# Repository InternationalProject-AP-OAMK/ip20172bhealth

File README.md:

# 2bhealth
International Project BEL / FIN to develop an e-Health prototype with application to read-out the users' heartrate

## Working Android Studio code:
https://github.com/InternationalProject-AP-OAMK/ip20172bhealth/tree/master/Android_Studio/_workingProject

## Hardware documentation:
https://github.com/InternationalProject-AP-OAMK/ip20172bhealth/tree/master/Hardware/

## Fitrax (Solo) downloadable in the Play Store:
https://play.google.com/store/apps/details?id=com.nickenkoen.fitraxfinaldemo
- tested with Xiaomi Mi5S, 5.15inch, 1920x1080p, Android 7.1.1
- tested with Samsung Galaxy S4 mini, 4.3inch, 960x540p, Android 4.4.4
- tested with Motorola Moto X, 4.7inch, 1280x720p, Android 6.0

## Fitrax (Team) downloadable in the Play Store:
https://play.google.com/store/apps/details?id=com.nickenkoen.fitraxfinalcoachdemo
- tested with Samsung Galaxy Note 10.1, 10.1 inch, 1280x800p, Android 5.0 

!! Layout can differ between devices !!

## How to install/use:
1. Download Fitrax Solo on smartphone
2. Open and login with a new teamname and username
3. Tap the BlueTooth logo and connect to the fitness tracker
4. In this dialog tap Heart Rate Service and Heart Rate Measurement
5. Go back to the Main Activity

6. If the device doensn't connect on the first time, try again.

7. Download Fitrax Team on tablet
8. Open app and fill in teamname (all CAPS) and connect

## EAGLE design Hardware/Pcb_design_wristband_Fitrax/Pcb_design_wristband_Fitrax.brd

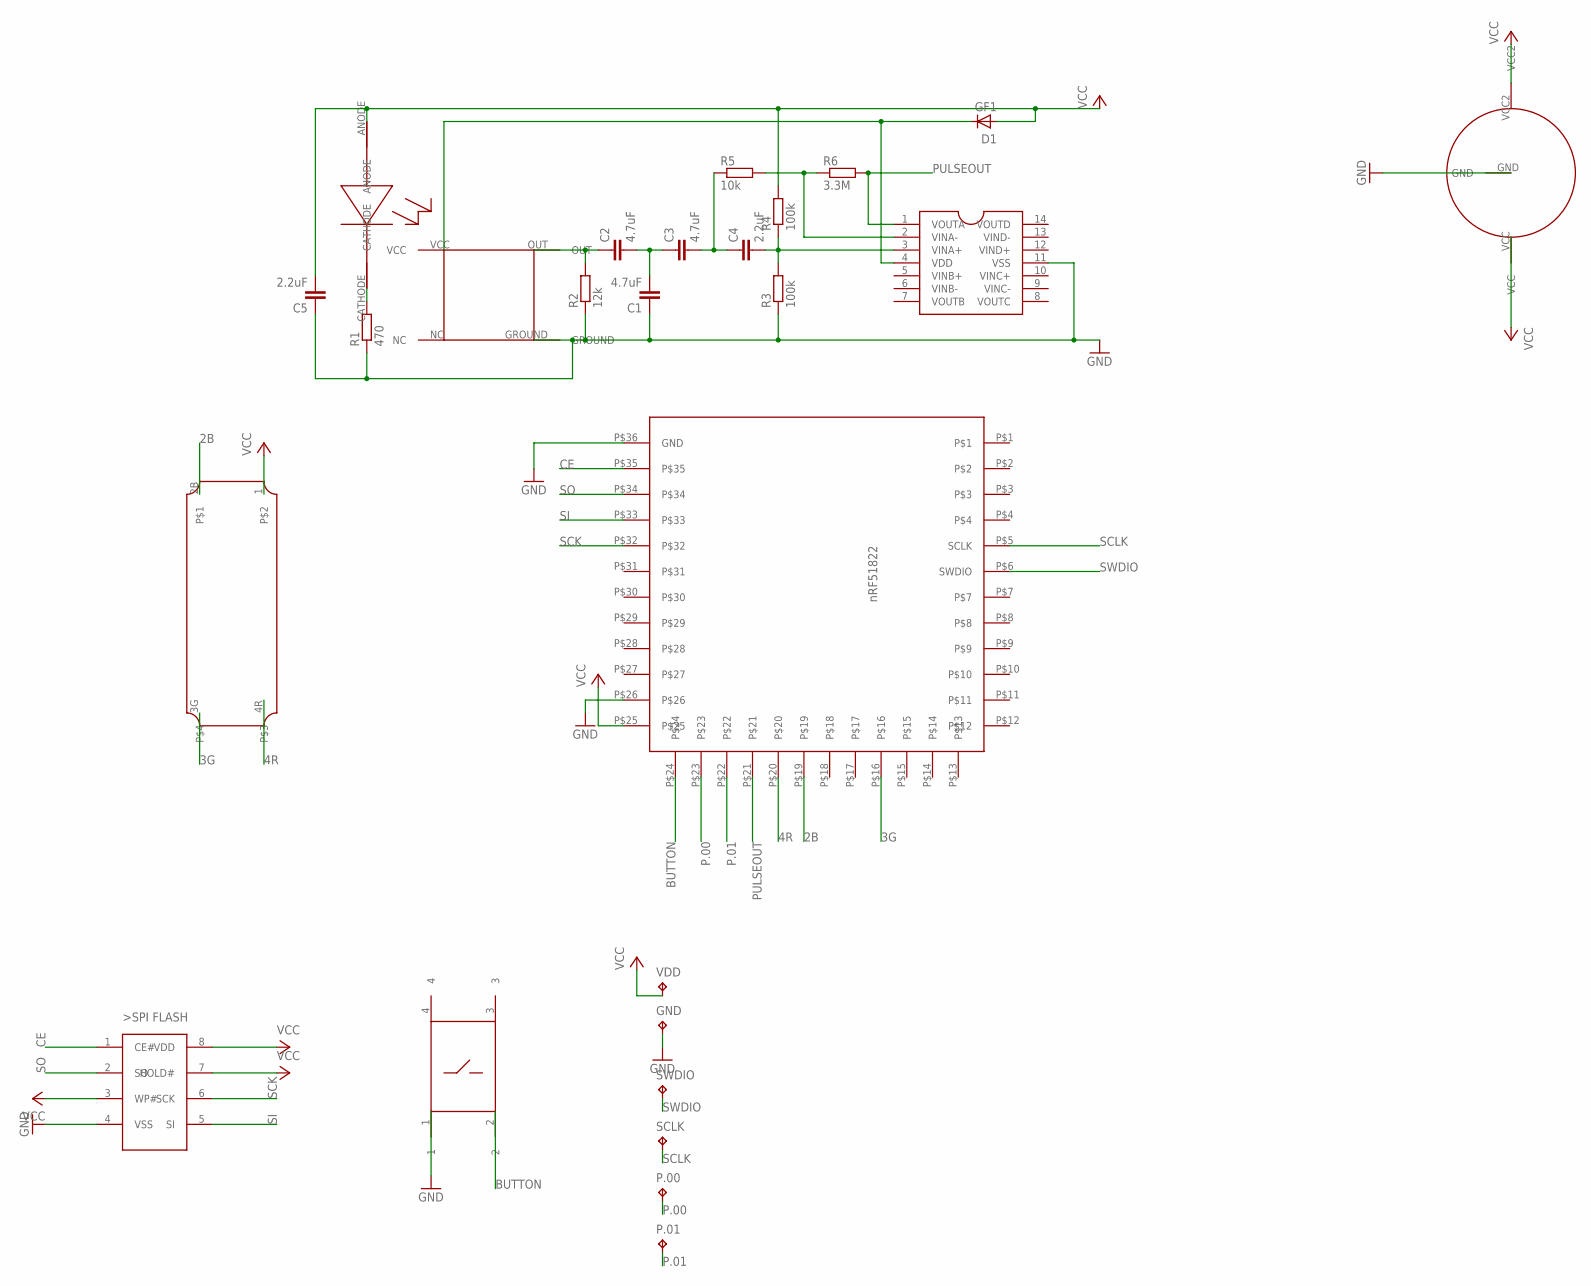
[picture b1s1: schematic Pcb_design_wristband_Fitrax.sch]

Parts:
C1, C2, C3: 4.7uF; C0805
C4, C5: 2.2uF; C0805
D1: GF1; SMA-DO214AC
GND: TPTP09SQ; TP09SQ
P.00, P.01: TPTP09SQ; TP09SQ
R1: 470; M0805
R2: 12k; M0805
R3, R4: 100k; M0805
R5: 10k; M0805
R6: 3.3M; M0805
SCLK: TPTP09SQ; TP09SQ
SWDIO: TPTP09SQ; TP09SQ
U$1: LIGHTSENSOR
U$2: OPAMP; TSSOP-14
U$3: GREENLED
U$4: BATTERY
U$5: NRF51822
U$6: BUTTON1
U$7: RGB
U$8: SPI_FLASH; SOIC-8
VDD: TPTP09SQ; TP09SQ

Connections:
2B: U$5.P$19, U$7.2B
3G: U$5.P$16, U$7.3G
4R: U$5.P$20
BUTTON: U$5.P$24, U$6.2
CE: U$5.P$35, U$8.1 (CE#)
GND: C1.1, C5.1, GND.TP, R1.1, R2.1, R3.1, U$1.GROUND, U$2.11 (VSS), U$4.GND, U$5.P$26, U$5.P$36 (GND), U$6.1, U$8.4 (VSS)
unnamed: C4.2, R3.2, R4.1, U$2.3 (VINA+)
unnamed: C3.2, C4.1, R5.1
unnamed: D1.K (C), U$1.VCC, U$2.4 (VDD)
unnamed: R5.2, R6.1, U$2.2 (VINA-)
unnamed: C1.2, C2.2, C3.1
unnamed: C2.1, R2.2, U$1.OUT
unnamed: R1.2, U$3.CATHODE
P.00: P.00.TP, U$5.P$23
P.01: P.01.TP, U$5.P$22
PULSEOUT: R6.2, U$2.1 (VOUTA), U$5.P$21
SCK: U$5.P$32, U$8.6 (SCK)
SCLK: SCLK.TP, U$5.P$5 (SCLK)
SI: U$5.P$33, U$8.5 (SI)
SO: U$5.P$34, U$8.2 (SO)
SWDIO: SWDIO.TP, U$5.P$6 (SWDIO)
VCC: C5.2, D1.A, R4.2, U$3.ANODE, U$4.VCC, U$5.P$25, U$7.1, U$8.3 (WP#), U$8.7 (HOLD#), U$8.8 (VDD), VDD.TP

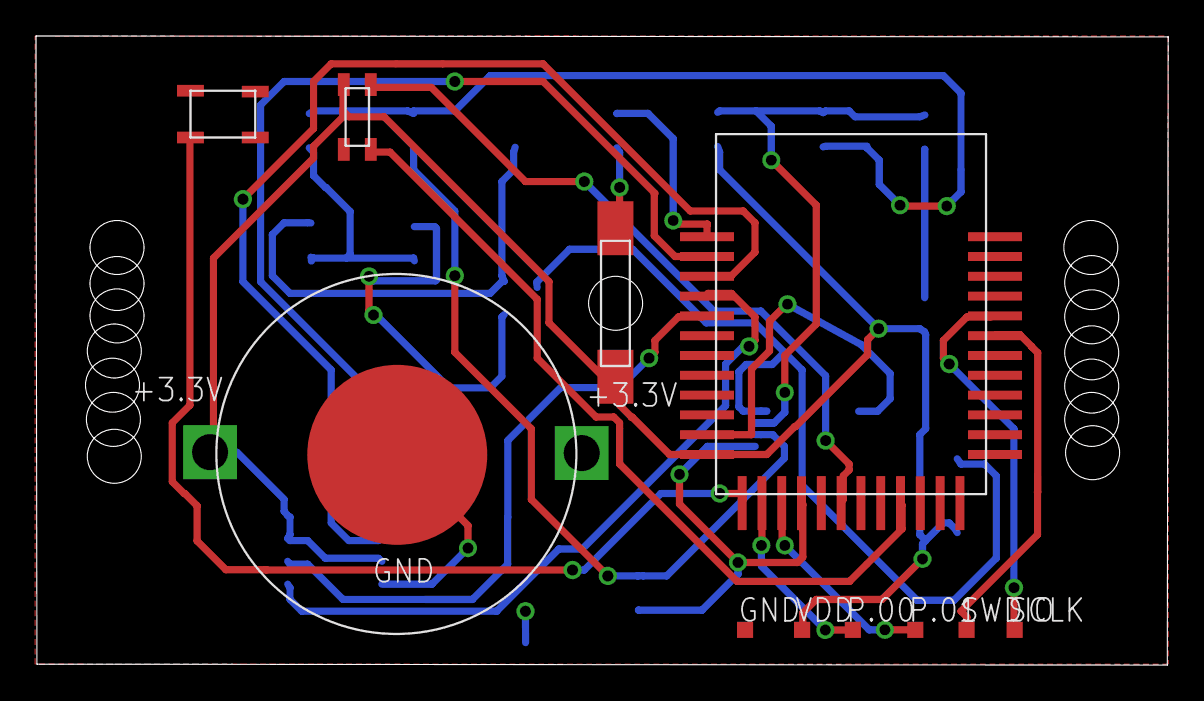
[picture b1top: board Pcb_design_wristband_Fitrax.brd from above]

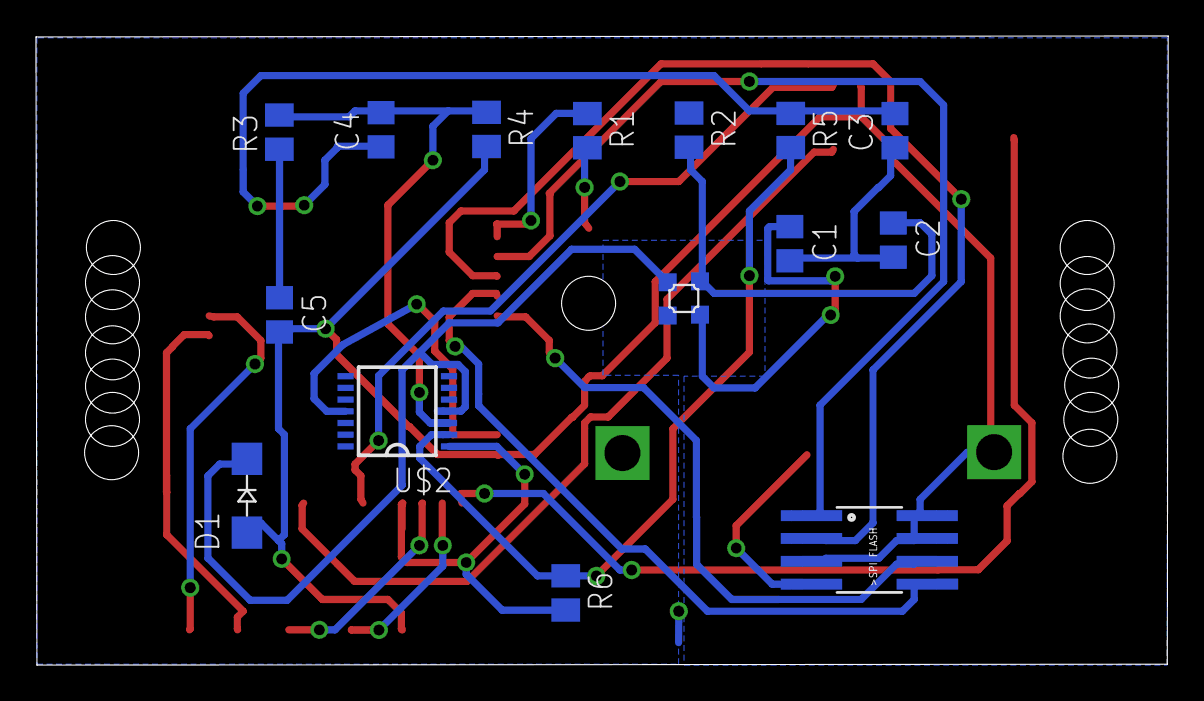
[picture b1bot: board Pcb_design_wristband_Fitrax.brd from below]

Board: 2 copper layers, 62.9 x 34.9 mm, 26 parts (15 on the bottom side), 21 nets.

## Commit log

2017-02-22 first commit to get data up-to-date
2017-02-22 first commit with pitch and mockups
2017-02-22 second commit to sync
2017-02-22 first commit with Android Studio as test
2017-02-22 added tutorial for use of git
2017-02-22 changed HOW TO GIT.md
2017-02-22 changed HOW TO GIT.md again
2017-02-22 added convert test data to graph
2017-02-22 first android code
2017-02-22 update HOW TO GIT
2017-02-22 android code graph
2017-03-08 logo square and round design, app with 3 buttons and every 10 seconds update location with small circle. Gonna test it right now
2017-03-09 files moved to correct folder
2017-03-10 Added a nice overview of the measured statistics
2017-03-15 Added speed to overview
2017-03-15 Added basic share possibilities
2017-03-15 Login Activity done and put in data will be transfered to new Intent. Next to do: store login credentials in Array when Register and check if credentials exist when Sign In
2017-03-22 Implemented stepcounter in the overview
2017-03-22 forgot 2 files xd
2017-03-22 implemented calories calculation in the overview
2017-03-22 Implemented all sidefeatures in 1 demo-app
2017-03-22 Implemented graph in demo-app
2017-03-22 Added fitraxCompleteKoen with all options, except for stepcounter (Nick) and Maps Activity (Nick). He got those in the Demo app. Will add them later myself so we have a full working demo
2017-03-22 last changes to Demo project
2017-03-24 upload sprint timings pdf
2017-03-24 app demo fully functioning except for: 1. facebook share button is under construction. trying to get it working on Android 7.1.1 - works on 4.4.4 // 2. MainActivity is .LAUNCHER in Manifest file. Thi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
2017-03-25 changed Facebook Share button do default Nick implemented - still not working on my Android 7.1.1. and my other Android 5.1.1. Gotta check this once more. Also: permission for GPS needs to be asked o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
2017-03-26 added powerpoint presentation for demo exam
2017-03-26 Presentation finished and added screenshots folder and more mockups and other image files which will be shown in the presentation itself
2017-03-26 Small change in presentation - added Finnish students name and deleted a duplicate sheet
2017-03-27 final version of presentation: made some changes in SplashScreen demo
2017-04-27 two different projects started: FitraxPart2Nick and FitraxPart2Koen - to keep things separated and avoid merge conflicts
2017-04-27 Database set-up. Can connect and login/register - works great. Only saves e-mail and password - needs to be done: save username + teamname and retrieve username and teamname during login
2017-05-04 added bluetooth sample app to test bluetooth connection without the complete/complex app
2017-05-11 busy with firebase. Got Auth ready and can save/retrieve username, but need to use 197609 and Auth.UID or getUID
2017-05-11 merged BluetoothPart-Nick into FitraxPart2Nick
2017-05-11 made some small changes to FitraxPart2Nick
2017-05-18 busy with getting HeartRate updated every x seconds in MainActivity with BroadCastReceiver and Thread
2017-05-23 added code for heartrate and the graph
2017-05-23 overschot die hij niet wou committen eerste keer.
2017-05-23 working bluetooth code
2017-05-23 hopefully working code
2017-05-23 Final Project FitraxFinalDemo (solo/user) and FitraxFinalCoachDemo (team/coach) working and cleaned up for so far. Only need to add HeartRateAverage to be calculated and posted into Database in MainA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
2017-05-24 Done
2017-05-30 Updated fitraxfinaldemo and fitraxfinalcoachdemo with signable apk code. Signed APK's and uploaded in Play Store
2017-05-30 added Hardware.
